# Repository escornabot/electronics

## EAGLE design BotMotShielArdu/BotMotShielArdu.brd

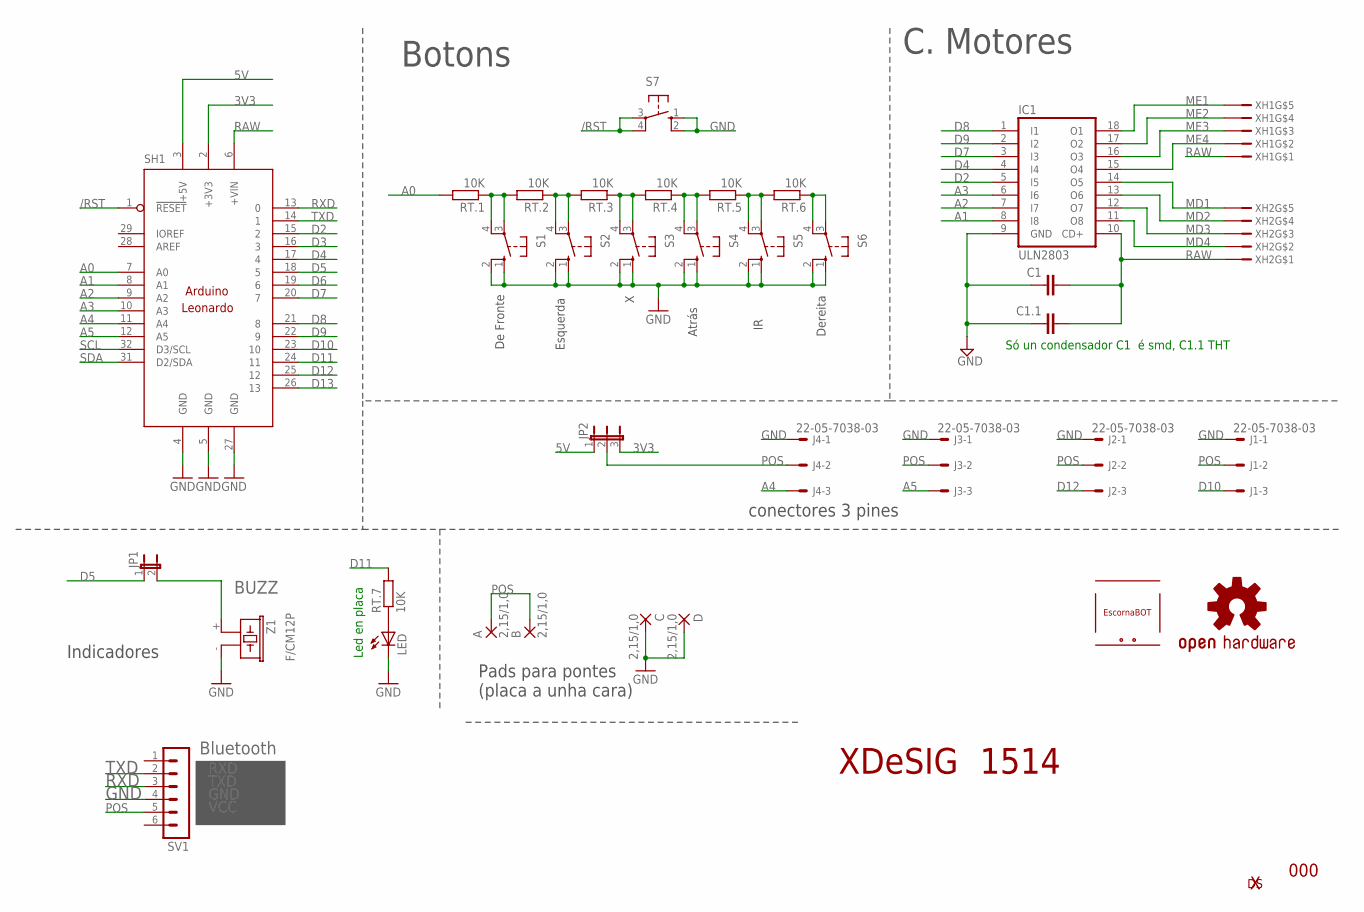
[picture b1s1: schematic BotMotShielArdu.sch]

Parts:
A: 2,15/1,0
B: 2,15/1,0
C: 2,15/1,0
C1: C-EUC1206; C1206
C1.1: C-EU025-024X044; C025-024X044
D: 2,15/1,0
IC1: ULN2803; DIL18
J1, J2, J3, J4: 22-05-7038-03; 7395-03
JP1: JP1E; JP1
JP2: JP2E; JP2
LED: LED5MM
LOGO4: OSHW-LOGOS; OSHW-LOGO-S
RT.1, RT.2, RT.3, RT.4, RT.5, RT.6, RT.7: 10K; 0204/7
S1, S2, S3, S4, S5, S6: B3F-40XX; B3F40XX_NH
S7: 10-XX; B3F-10XX
SH1: ARDUINO_LEONARDO; LEONARDO
SV1: MA06-1
U$1: ESCORNABOT; ESCORNA_PEQUE
U$3: XDESIG1; XDESIG_CU
XH1, XH2: B5B-XH-A
Z1: F/CM12P

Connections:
3V3: JP2.3, SH1.2 (+3V3)
5V: JP2.1, SH1.3 (+5V)
/RST: S7.3, S7.4 (P1), SH1.1 (!RESET)
A0: RT.1.2, SH1.7 (A0)
A1: IC1.8 (I8), SH1.8 (A1)
A2: IC1.7 (I7), SH1.9 (A2)
A3: IC1.6 (I6), SH1.10 (A3)
A4: J4.3, SH1.11 (A4)
A5: J3.3, SH1.12 (A5)
D2: IC1.5 (I5), SH1.15 (2)
D3: SH1.16 (3)
D4: IC1.4 (I4), SH1.17 (4)
D5: JP1.1, SH1.18 (5)
D6: SH1.19 (6)
D7: IC1.3 (I3), SH1.20 (7)
D8: IC1.1 (I1), SH1.21 (8)
D9: IC1.2 (I2), SH1.22 (9)
D10: J1.3, SH1.23 (10)
D11: RT.7.2, SH1.24 (11)
D12: J2.3, SH1.25 (12)
D13: SH1.26 (13)
GND: C.1, C1.1, C1.1.1, D.1, IC1.9 (GND), J1.1, J2.1, J3.1, J4.1, LED.K (C), S1.1 (S), S1.2 (S1), S2.1 (S), S2.2 (S1), S3.1 (S), S3.2 (S1), S4.1 (S), S4.2 (S1), S5.1 (S), S5.2 (S1), S6.1 (S), S6.2 (S1), S7.1 (S), S7.2 (S1), SH1.4 (GND), SH1.5 (GND), SH1.27 (GND), SV1.4, Z1.- (2)
MD1: IC1.14 (O5), XH2.P$5
MD2: IC1.13 (O6), XH2.P$4
MD3: IC1.12 (O7), XH2.P$3
MD4: IC1.11 (O8), XH2.P$2
ME1: IC1.18 (O1), XH1.P$5
ME2: IC1.17 (O2), XH1.P$4
ME3: IC1.16 (O3), XH1.P$3
ME4: IC1.15 (O4), XH1.P$2
unnamed: LED.A, RT.7.1
unnamed: RT.6.1, S6.3, S6.4 (P1)
unnamed: RT.1.1, RT.2.2, S1.3, S1.4 (P1)
unnamed: JP1.2, Z1.+ (1)
unnamed: RT.5.1, RT.6.2, S5.3, S5.4 (P1)
unnamed: RT.4.1, RT.5.2, S4.3, S4.4 (P1)
unnamed: RT.3.1, RT.4.2, S3.3, S3.4 (P1)
unnamed: RT.2.1, RT.3.2, S2.3, S2.4 (P1)
POS: A.1, B.1, J1.2, J2.2, J3.2, J4.2, JP2.2, SV1.5
RAW: C1.2, C1.1.2, IC1.10 (CD+), SH1.6 (+VIN), XH1.P$1, XH2.P$1
RXD: SH1.13 (0), SV1.3
SCL: SH1.32 (D3/SCL)
SDA: SH1.31 (D2/SDA)
TXD: SH1.14 (1), SV1.2

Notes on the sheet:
Só un condensador C1 é smd, C1.1 THT
De Fronte
Esquerda
Dereita
Atrás
Led en placa
BUZZ
Bluetooth
RXD
TXD
GND
VCC
Botons
C. Motores
conectores 3 pines
Indicadores
Pads para pontes (placa a unha cara)
XDeSIG
1514
000

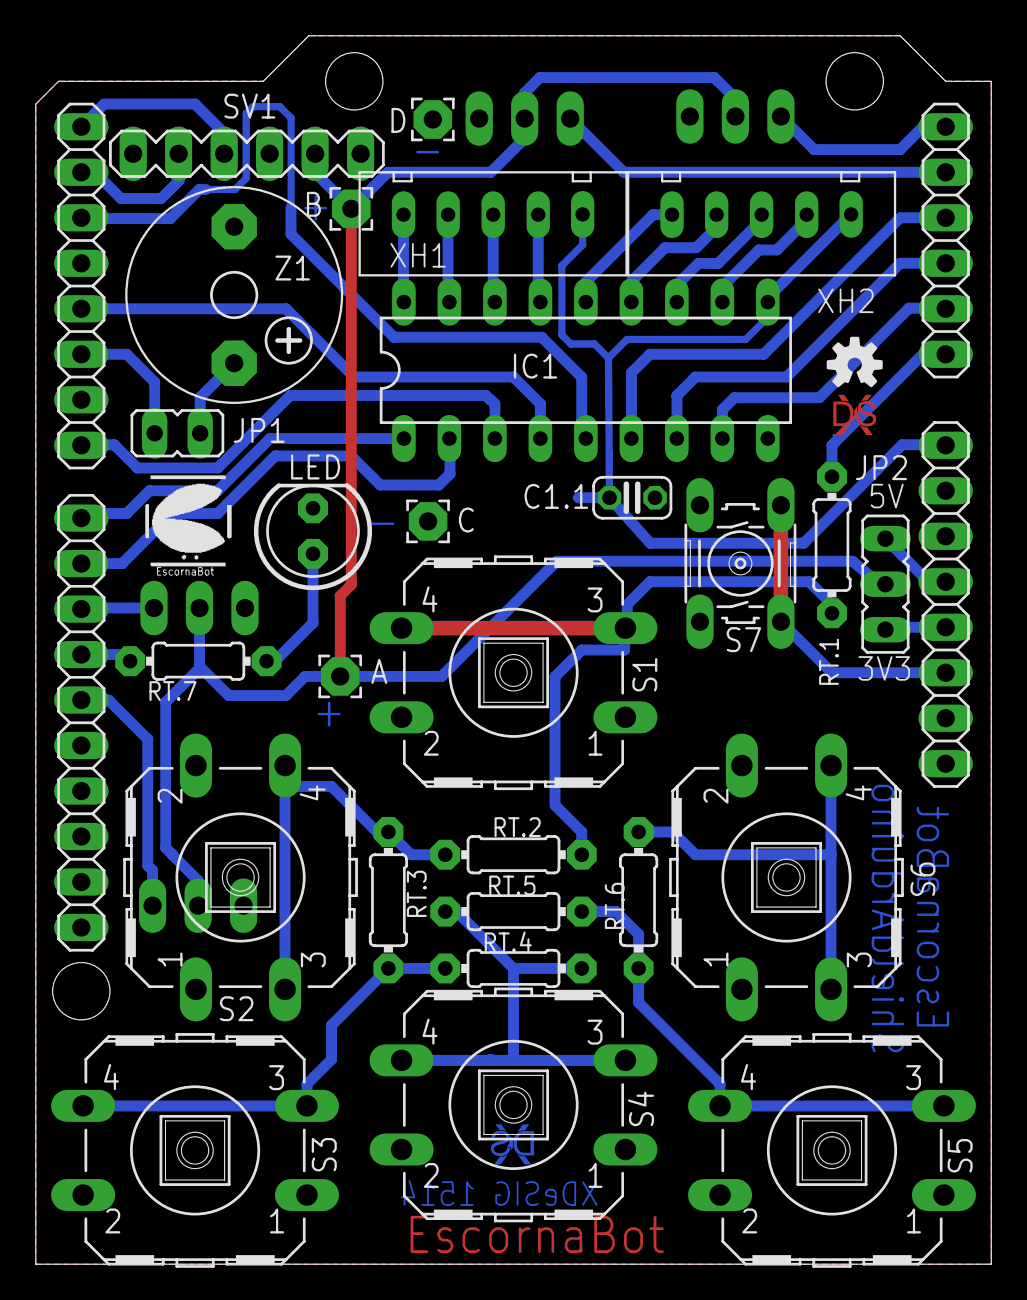
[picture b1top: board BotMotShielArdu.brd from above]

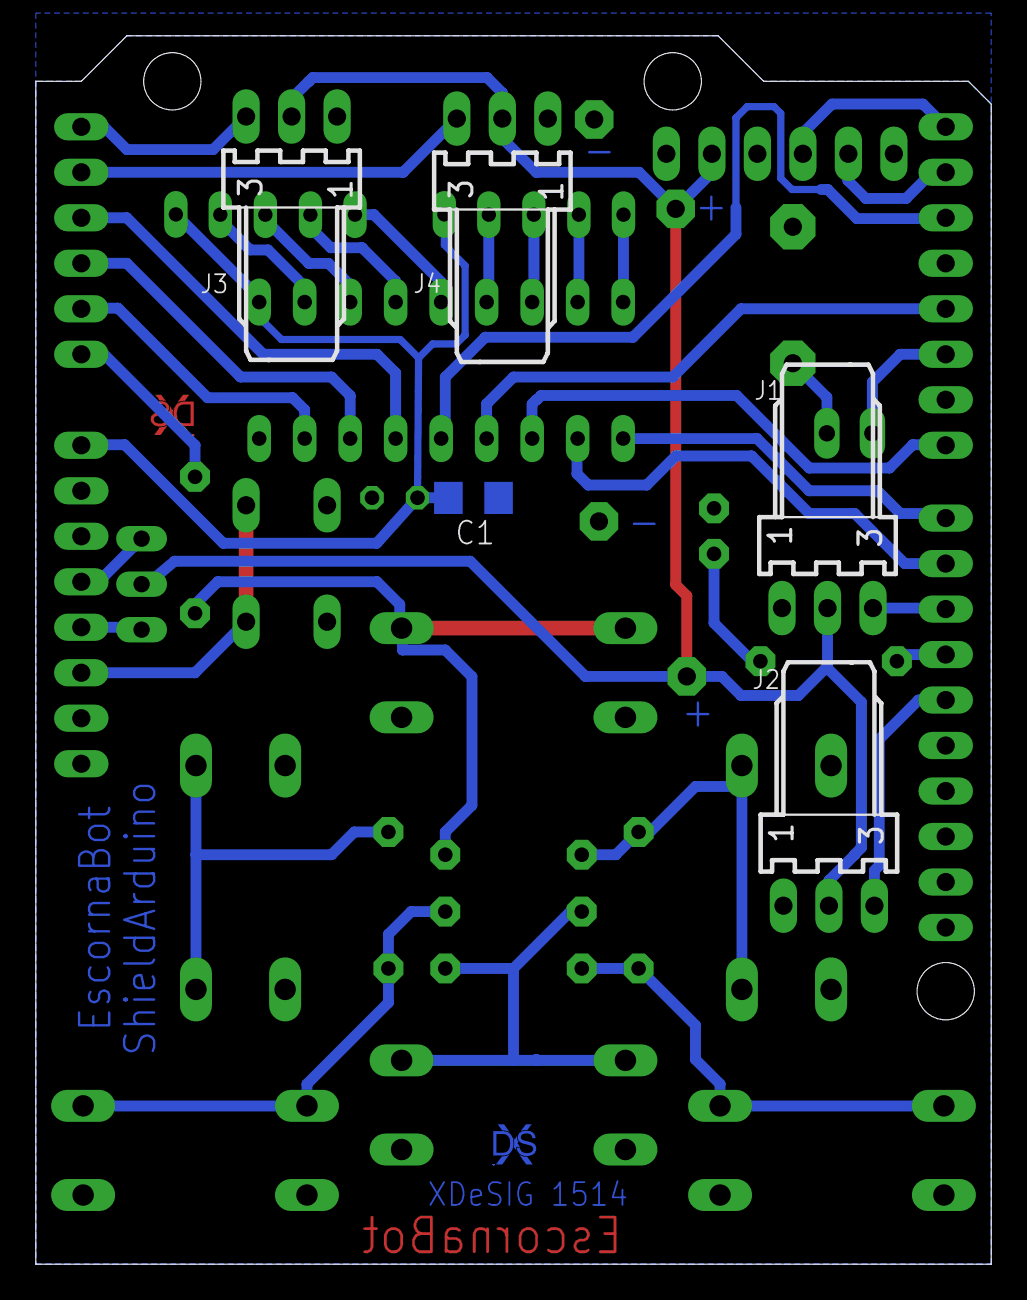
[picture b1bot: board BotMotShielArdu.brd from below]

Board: 2 copper layers, 53.3 x 68.6 mm, 37 parts (6 on the bottom side), 39 nets.

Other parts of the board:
U$2: XDESIG1; XDESIG_CU

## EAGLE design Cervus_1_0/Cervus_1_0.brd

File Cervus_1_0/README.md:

# Cervus version 1.0

* Author: [XDeSIG][SITE]
* License: [Creative Commons BY-SA][CCBYSA]

![Render EscornaShield Keypad][RENDER]

[CCBYSA]: http://creativecommons.org/licenses/by-sa/4.0/
[SITE]: https://sites.google.com/site/xdesig/
[RENDER]: Cervus_1_0.jpg

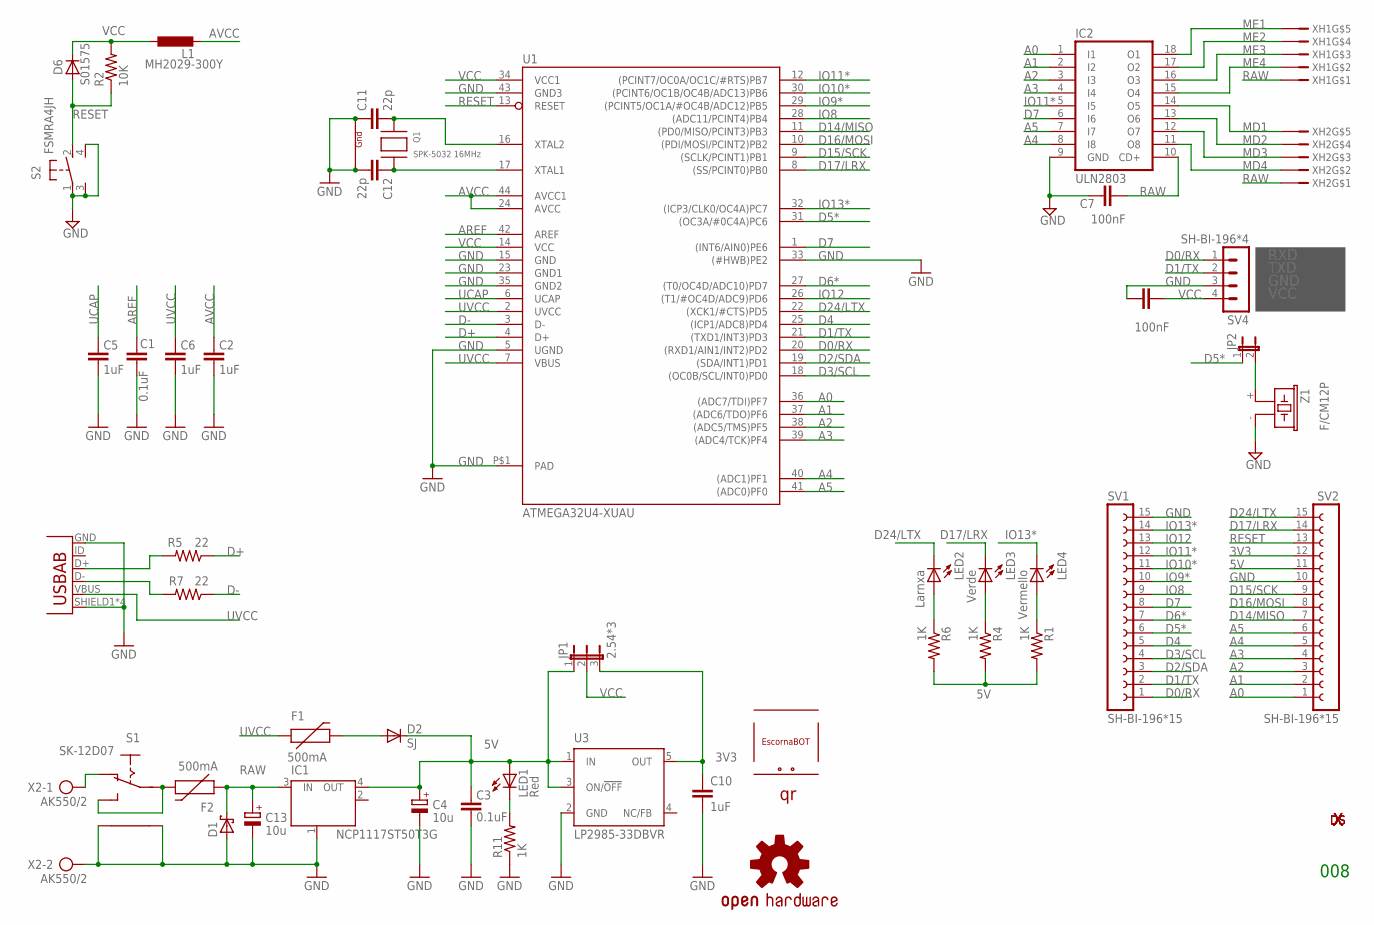
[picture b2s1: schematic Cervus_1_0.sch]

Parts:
C1, C3: 0.1uF; 0603-CAP
C2, C5, C6, C10: 1uF; 0603-CAP
C4, C13: 10u; SMC_B
C7, C8: 100nF; C0603K
C11, C12: 22p; C0603-ROUND
D1: SCHOTTKY-DIODESMA; SMA
D2: SJ; SOD-323
D6: S01575; SOD-323
F1, F2: 500mA; PTC-1206
IC1: NCP1117ST50T3G; SOT223
IC2: ULN2803; DIL18
JP1: 2.54*3; JP2
JP2: JP1E; JP1
L1: MH2029-300Y; L2012C
LED1: Red; LED-0603
LED2: Larnxa; LED-0603
LED3: Verde; LED-0603
LED4: Vermello; LED-0603
LOGO1: OSHW-LOGOS; OSHW-LOGO-S
Q1: SPK-5032 16MHz; NX3225
R1, R4, R6, R11: 1K; 0603-RES
R2: 10K; 0603-RES
R5, R7: 22; 0603-RES
S1: SK-12D07
S2: FSMRA4JH; B3F-31XX
SV1, SV2: SH-BI-196*15; FE15
SV4: SH-BI-196*4; MA04-1
U1: ATMEGA32U4-XUAU; TQFP44-PAD
U2: MICRO USB; USB-AB-MICRO-SMD
U3: LP2985-33DBVR; SOT23-DBV
U$2: XDESIG; XDESIG_CU_2
U$3: ESCORNABOT; ESCORNA_PEQUE
U$5: XDESIG21; XDESIG
U$6: QR25; ESCORNA_QR25
X2: AK550/2
XH1, XH2: XH2.54-5P; B5B-XH-A
Z1: F/CM12P

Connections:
3V3: C10.1, JP1.3, SV2.12, U3.5 (OUT)
5V: C3.2, C4.+, D2.1 (C), IC1.4 (OUT), JP1.1, LED1.A, R1.2, R4.2, R6.2, SV2.11, U3.1 (IN), U3.3 (ON/!OFF)
A0: IC2.1 (I1), SV2.1, U1.36 ((ADC7/TDI)PF7)
A1: IC2.2 (I2), SV2.2, U1.37 ((ADC6/TDO)PF6)
A2: IC2.3 (I3), SV2.3, U1.38 ((ADC5/TMS)PF5)
A3: IC2.4 (I4), SV2.4, U1.39 ((ADC4/TCK)PF4)
A4: IC2.8 (I8), SV2.5, U1.40 ((ADC1)PF1)
A5: IC2.7 (I7), SV2.6, U1.41 ((ADC0)PF0)
AREF: C1.2, U1.42 (AREF)
AVCC: C2.2, L1.2, U1.24 (AVCC), U1.44 (AVCC1)
D0/RX: SV1.1, SV4.1, U1.20 ((RXD1/AIN1/INT2)PD2)
D1/TX: SV1.2, SV4.2, U1.21 ((TXD1/INT3)PD3)
D2/SDA: SV1.3, U1.19 ((SDA/INT1)PD1)
D3/SCL: SV1.4, U1.18 ((OC0B/SCL/INT0)PD0)
D4: SV1.5, U1.25 ((ICP1/ADC8)PD4)
D5*: JP2.1, SV1.6, U1.31 ((OC3A/#0C4A)PC6)
D6*: SV1.7, U1.27 ((T0/OC4D/ADC10)PD7)
D7: IC2.6 (I6), SV1.8, U1.1 ((INT6/AIN0)PE6)
D14/MISO: SV2.7, U1.11 ((PD0/MISO/PCINT3)PB3)
D15/SCK: SV2.9, U1.9 ((SCLK/PCINT1)PB1)
D16/MOSI: SV2.8, U1.10 ((PDI/MOSI/PCINT2)PB2)
D17/LRX: LED3.C, SV2.14, U1.8 ((SS/PCINT0)PB0)
D24/LTX: LED2.C, SV2.15, U1.22 ((XCK1/#CTS)PD5)
D+: R5.1, U1.4 (D+)
D-: R7.1, U1.3 (D-)
GND: C1.1, C2.1, C3.1, C4.-, C5.1, C6.1, C7.1, C8.1, C10.2, C11.1, C12.2, C13.-, D1.A, IC1.1 (GND/ADJ), IC2.9 (GND), Q1.2 (G2), Q1.4 (G1), R11.1, S1.P$4, S1.P$5, S2.1, S2.3 (CH2), S2.4 (CH1), SV1.15, SV2.10, SV4.3, U1.5 (UGND), U1.15 (GND), U1.23 (GND1), U1.33 ((#HWB)PE2), U1.35 (GND2), U1.43 (GND3), U1.P$1 (PAD), U2.GND, U2.SHIELD1 (SHIELD), U2.SHIELD2 (SHIELD), U2.SHIELD3 (SHIELD), U2.SHIELD4 (SHIELD), U3.2 (GND), X2.2, Z1.- (2)
IO8: SV1.9, U1.28 ((ADC11/PCINT4)PB4)
IO9*: SV1.10, U1.29 ((PCINT5/OC1A/#OC4B/ADC12)PB5)
IO10*: SV1.11, U1.30 ((PCINT6/OC1B/OC4B/ADC13)PB6)
IO11*: IC2.5 (I5), SV1.12, U1.12 ((PCINT7/OC0A/OC1C/#RTS)PB7)
IO12: SV1.13, U1.26 ((T1/#OC4D/ADC9)PD6)
IO13*: LED4.C, SV1.14, U1.32 ((ICP3/CLK0/OC4A)PC7)
MD1: IC2.14 (O5), XH2.P$5
MD2: IC2.13 (O6), XH2.P$4
MD3: IC2.12 (O7), XH2.P$3
MD4: IC2.11 (O8), XH2.P$2
ME1: IC2.18 (O1), XH1.P$5
ME2: IC2.17 (O2), XH1.P$4
ME3: IC2.16 (O3), XH1.P$3
ME4: IC2.15 (O4), XH1.P$2
unnamed: F2.2, S1.P$1, S1.P$3 (S)
unnamed: LED2.A, R6.1
unnamed: D2.2 (A), F1.2
unnamed: LED3.A, R4.1
unnamed: LED4.A, R1.1
unnamed: R7.2, U2.D-
unnamed: S1.P$2 (O), X2.1
unnamed: R5.2, U2.D+
unnamed: C12.1, Q1.3 (X2), U1.17 (XTAL1)
unnamed: LED1.C, R11.2
unnamed: JP2.2, Z1.+ (1)
RAW: C7.2, C13.+, D1.C, F2.1, IC1.3 (IN), IC2.10 (CD+), XH1.P$1, XH2.P$1
RESET: D6.2 (A), R2.1, S2.2 (S), SV2.13, U1.13 (RESET)
UCAP: C5.2, U1.6 (UCAP)
UVCC: C6.2, F1.1, U1.2 (UVCC), U1.7 (VBUS), U2.VBUS
VCC: C8.2, D6.1 (C), JP1.2, L1.1, R2.2, SV4.4, U1.14 (VCC), U1.34 (VCC1)
XTAL3: C11.2, Q1.1 (X1), U1.16 (XTAL2)

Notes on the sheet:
RXD
TXD
GND
VCC
008

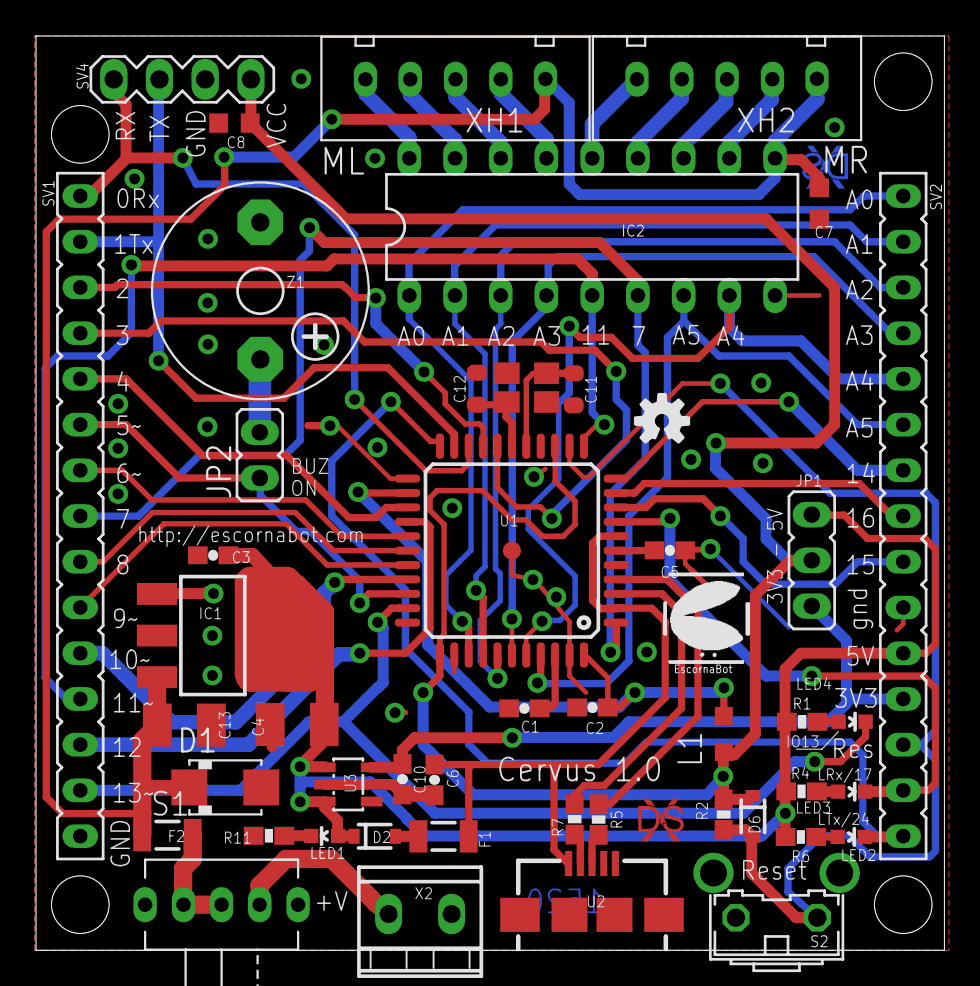
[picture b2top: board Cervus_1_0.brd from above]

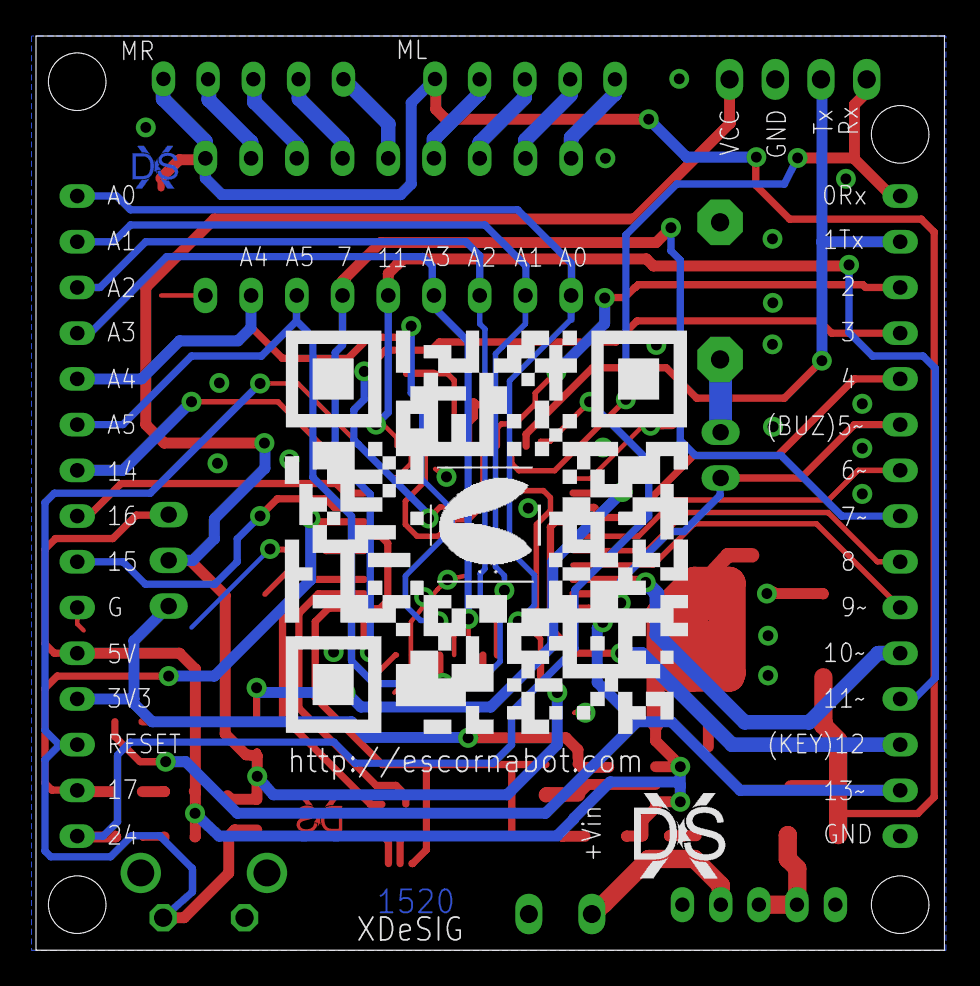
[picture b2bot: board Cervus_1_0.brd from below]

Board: 2 copper layers, 50.5 x 50.8 mm, 52 parts (3 on the bottom side), 57 nets.

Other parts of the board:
U$1: XDESIG; XDESIG_CU_2

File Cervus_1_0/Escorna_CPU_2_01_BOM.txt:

artlist exported from D:/PROXECTOS/Escorna_bot/Escorna_CPU_2.0/Escorna_CPU2_01/Escorna_CPU_2_01.sch at 16/05/2015 20:14:45

Part  Value           Device            Package          Description                                                                                                                                                                                                        MF MPN      OC_FARNELL OC_NEWARK
C1    0.1uF           CAP0603-CAP       0603-CAP         Capacitor
C2    1uF             CAP0603-CAP       0603-CAP         Capacitor
C3    0.1uF           CAP0603-CAP       0603-CAP         Capacitor
C4    10u             CPOL-EUSMCB       SMC_B            POLARIZED CAPACITOR, European symbol
C5    1uF             CAP0603-CAP       0603-CAP         Capacitor
C6    1uF             CAP0603-CAP       0603-CAP         Capacitor
C7    100nF           C-EUC0603K        C0603K           CAPACITOR, European symbol
C8    100nF           C-EUC0603K        C0603K           CAPACITOR, European symbol
C10   1uF             CAP0603-CAP       0603-CAP         Capacitor
C11   22p             C-EUC0603         C0603-ROUND      CAPACITOR, European symbol
C12   22p             C-EUC0603         C0603-ROUND      CAPACITOR, European symbol
C13   10u             CPOL-EUSMCB       SMC_B            POLARIZED CAPACITOR, European symbol
D1                    SCHOTTKY-DIODESMA SMA              Schottky Diode
D2    SJ              DIODESOD          SOD-323          Diode
D6    S01575          DIODESOD          SOD-323          Diode
F1    500mA           PTCSMD            PTC-1206         Resettable Fuse PTC
F2    500mA           PTCSMD            PTC-1206         Resettable Fuse PTC
IC1   NCP1117ST50T3G  MC33269ST-3.3T3   SOT223           Adjustable Output Low Dropout Voltage Regulator 800 mA
IC2   ULN2803         ULN2803A"         DIL18            DRIVER ARRAY
JP1   2.54*3          JP2E              JP2              JUMPER
JP2                   JP1E              JP1              JUMPER
L1    MH2029-300Y     L-EUL2012C        L2012C           INDUCTOR, European symbol
LED1  Red             LED0603           LED-0603         LEDs
LED2  Larnxa          LED0603           LED-0603         LEDs
LED3  Verde           LED0603           LED-0603         LEDs
LED4  Vermello        LED0603           LED-0603         LEDs
Q1    SPK-5032 16MHz  XTAL-4-3225       NX3225           Classic 4-pin 3.2 x 2.5mm crystal
R1    1K              RESISTOR0603-RES  0603-RES         Resistor
R2    10K             RESISTOR0603-RES  0603-RES         Resistor
R4    1K              RESISTOR0603-RES  0603-RES         Resistor
R5    22              RESISTOR0603-RES  0603-RES         Resistor
R6    1K              RESISTOR0603-RES  0603-RES         Resistor
R7    22              RESISTOR0603-RES  0603-RES         Resistor
R11   1K              RESISTOR0603-RES  0603-RES         Resistor
S1    SK-12D07        SK12F14D          SK-12D07
S2    FSMRA4JH        31-XX             B3F-31XX
SV1   SH-BI-196*15    FE15-1            FE15             FEMALE HEADER                                                                                                                                                                                                                  unknown    unknown
SV2   SH-BI-196*15    FE15-1            FE15             FEMALE HEADER                                                                                                                                                                                                                  unknown    unknown
SV4   SH-BI-196*4     MA04-1            MA04-1           PIN HEADER                                                                                                                                                                                                                     unknown    unknown

U1    ATMEGA32U4-XUAU ATMEGA32U4-XUAU   TQFP44-PAD
U2    MICRO USB       USB-AB            USB-AB-MICRO-SMD This is a USB AB connector that is compatible with USB OTG. i.e. this connector can serve as a host or device
U3    LP2985-33DBVR   LP2985-XXDBVR33   SOT23-DBV        ULTRALOW-POWER 50-mA LOW-DROPOUT LINEAR REGULATORS
X2    AK550/2         AK550/2           AK550/2          CONNECTOR                                                                                                                                                                                                                      unknown    unknown
XH1   XH2.54-5P       B5B-XH-A          B5B-XH-A
XH2   XH2.54-5P       B5B-XH-A          B5B-XH-A
Z1    F/CM12P         F/CM12P           F/CM12P          BUZZER 12mm Source: Buerklin                                                                                                                                                                                                        unknown    unknown

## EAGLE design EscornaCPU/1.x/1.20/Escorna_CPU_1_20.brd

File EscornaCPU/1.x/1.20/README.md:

## Escorna CPU 1.20

It allows to include an Arduino Uno for the control of the robot, an ESP-01 or Bluetooth (for communications).
You can connect them to different keypads to manage the robot, I recommend the [E_KEYPAD_2.20]

## License

Every content in this repo, otherwise specified under subdirectories, is
licensed under [CERN Open Hardware Licence -W- V2][OHL-W-V2].
(by [XDeSIG][XDE01])

## To buy boards

Developer doesn't produce boards to get money. [provider]

Are you a board provider? Please, send us your buyer's guide! xdesig@gmail.com

[XDE01]: https://twitter.com/xdesig
[provider]: https://www.pcbway.com/project/shareproject/W50475ASN23_Escorna_CPU_1_20.html
[LICENSEcc]: https://creativecommons.org/licenses/by-sa/3.0/es
[OHL-W-V2]: https://ohwr.org/project/cernohl/wikis/Documents/CERN-OHL-version-2
[E_KEYPAD_2.20]: https://github.com/xdesig/escornabot-electronics/tree/master/Electronics/E_KEYPAD/E_KEYPAD_2.20

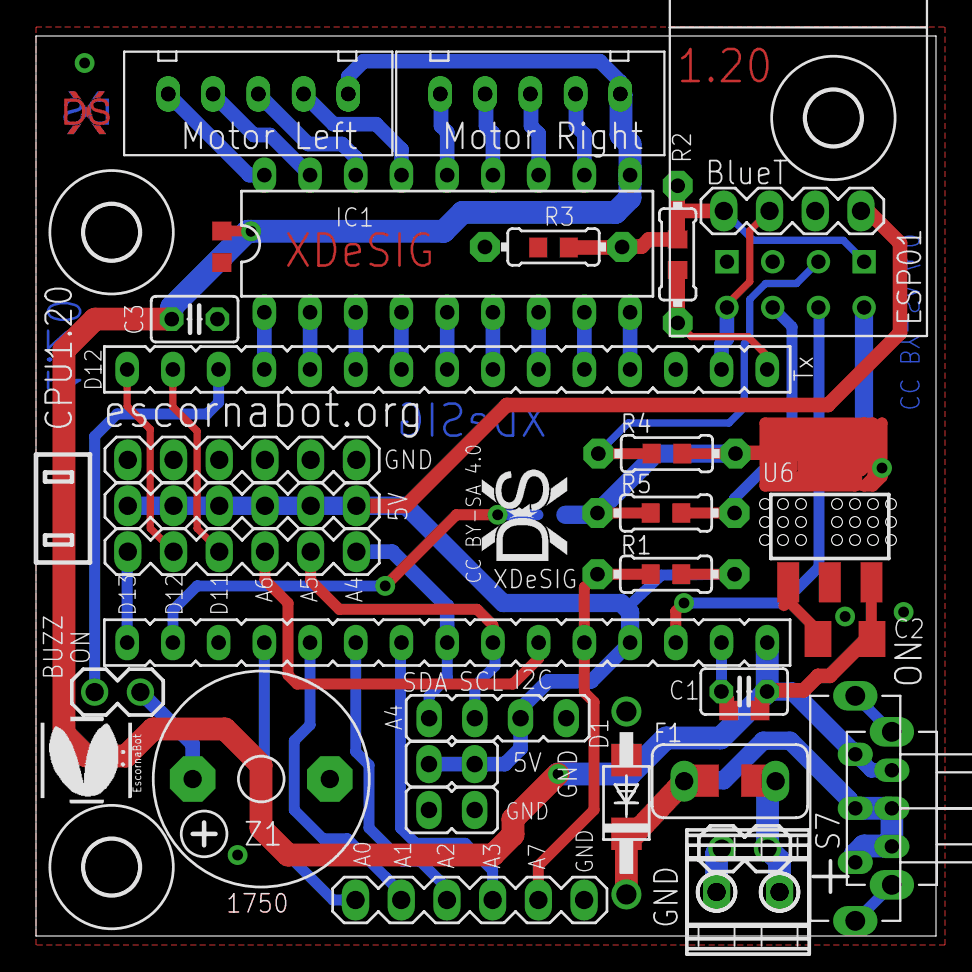
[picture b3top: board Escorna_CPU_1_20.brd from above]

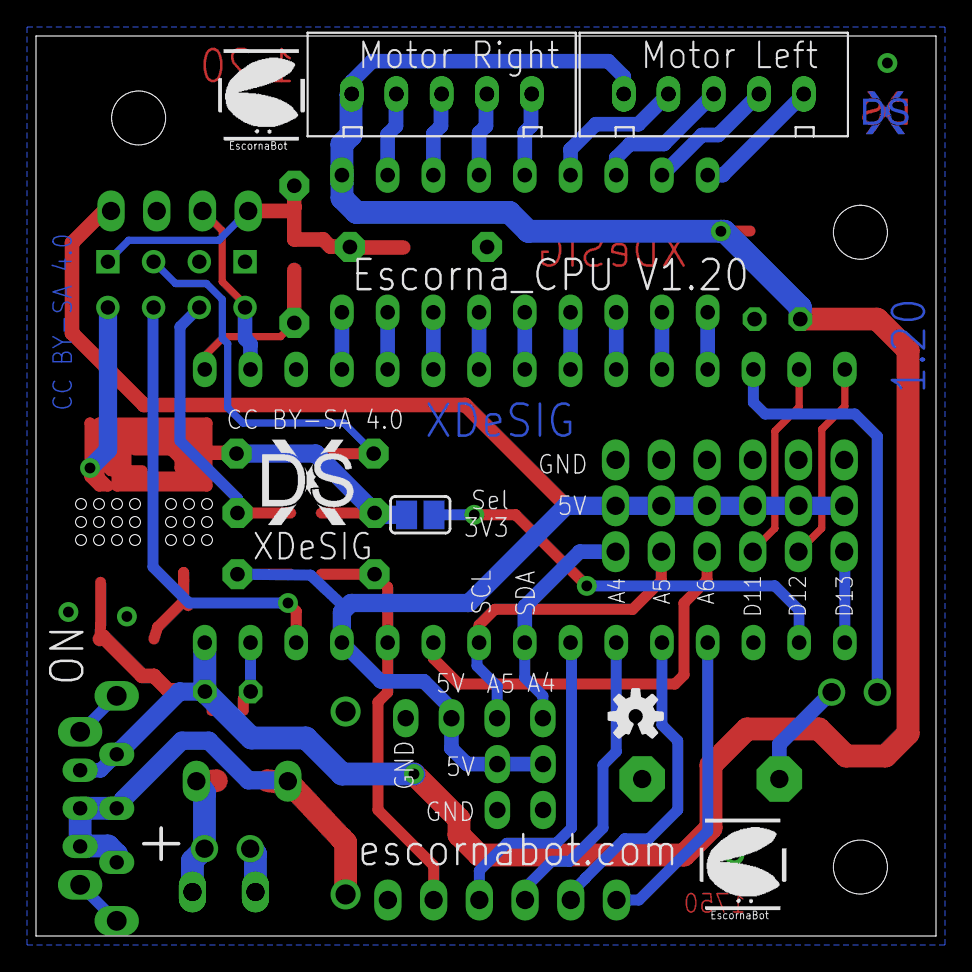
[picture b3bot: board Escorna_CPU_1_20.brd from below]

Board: 2 copper layers, 50.0 x 50.0 mm, 55 parts (8 on the bottom side), 44 nets.

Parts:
C1, C3: 100nF; C025-025X050
C1.1, C3.1: 100nF; C0603K
C2: 1uF; C1206K
D1: 1N5817; DO41-10
D1.1: M7; SMA-DO214AC
ESC, ESC1, ESC2: ESCORNABOT; ESCORNA_PEQUE
F1: PFRA.050; TE5
F1.1: PolySwitch; R1206
H3, H4: H3.0; 3,0
H7: MOUNT-HOLE3.0; 3,0
IC1: ULN2803; DIL18
JP1, JP2: 1X02
JP3, JP4: JP1
JP5: JP4
LOGO2: OSHW-LOGOS; OSHW-LOGO-S
R1, R2, R4, R5: 10K; 0204/7
R1.1, R2.1, R4.1, R5.1: 10K; R0603
R3: 18K; 0204/7
R3.1: 18K; R0603
S7: SK12F14; ESCORNA_SK-12F14-G
S7.1: SK12D07; ESCORNA_SK-12D07
SJ1: SJ
SV1, SV2: 1x15 SOCKET STRIP; CON-LSTA_FE15
SV3, SV4, SV5, SV6: MA06-1
U2: ESP01
U3: MA04-1
U6: 1117-3.3; SOT223
U$1, U$13: XDESIG_XDESIG21; XDESIG_XDESIG
X1, X1.1: AK550/2
XDS, XDS1: XDESIG; XDESIG_CU_2
XH1, XH2, XH3, XH4: B5B-XH-A
Z1: CFG12; F/CM12P

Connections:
3.3V: SJ1.2, SV2.14
3V3: R4.1, R4.1.1, R5.1, R5.1.1, SJ1.1, U2.VCC, U6.4
5V: JP3.1, JP3.2, JP5.3, R1.1, R1.1.1, SV2.4, SV4.1, SV4.2, SV4.3, SV4.4, SV4.5, SV4.6, U3.4
A0: SV2.12, SV6.1
A1: SV2.11, SV6.2
A2: SV2.10, SV6.3
A3: SV2.9, SV6.4
A4: JP5.1, SV2.8, SV3.1
A5: JP5.2, SV2.7, SV3.2
A6: SV2.6, SV3.3
A7: R1.2, R1.1.2, SV2.5, SV6.5
CH: R4.2, R4.1.2, U2.GPIO0
D2: IC1.8, SV1.5
D3: IC1.7, SV1.6
D4: IC1.6, SV1.7
D5: IC1.5, SV1.8
D6: IC1.4, SV1.9
D7: IC1.3, SV1.10
D8: IC1.2, SV1.11
D9: IC1.1, SV1.12
D10: JP1.2, SV1.13
D11: SV1.14, SV3.4
D12: SV1.15, SV3.5
D13: SV2.15, SV3.6
GND: C1.2, C1.1.1, C2.1, C3.1, C3.1.1, D1.A, D1.1.A, IC1.9, JP2.1, JP4.1, JP4.2, JP5.4, R3.2, R3.1.1, SV1.4, SV2.2, SV5.1, SV5.2, SV5.3, SV5.4, SV5.5, SV5.6, SV6.6, U2.GND, U3.3, U6.1, X1.1, X1.1.2, Z1.-
ML1: IC1.18, XH1.P$5, XH3.P$5
ML2: IC1.17, XH1.P$4, XH3.P$4
ML3: IC1.16, XH1.P$3, XH3.P$3
ML4: IC1.15, XH1.P$2, XH3.P$2
MR1: IC1.14, XH2.P$5, XH4.P$5
MR2: IC1.13, XH2.P$4, XH4.P$4
MR3: IC1.12, XH2.P$3, XH4.P$3
MR4: IC1.11, XH2.P$2, XH4.P$2
unnamed: R5.2, R5.1.2, U2.CH_PD
unnamed: JP1.1, Z1.+
unnamed: F1.1, F1.1.1, JP2.2, X1.2, X1.1.1
unnamed: S7.P$4, S7.1.P$4
unnamed: S7.P$5, S7.1.P$5
RAW: C1.1, C1.1.2, C2.2, C3.2, C3.1.2, IC1.10, S7.P$2, S7.1.P$2, SV2.1, U6.3, XH1.P$1, XH2.P$1, XH3.P$1, XH4.P$1
RST: SV2.3, U2.RST
RX: SV1.2, U2.TX, U3.2
TX: R2.1, R2.1.1, SV1.1
TX3V3: R2.2, R2.1.2, R3.1, R3.1.2, U2.RX, U3.1
VIN: D1.C, D1.1.K, F1.2, F1.1.2, S7.P$1, S7.P$3, S7.1.P$1, S7.1.P$3

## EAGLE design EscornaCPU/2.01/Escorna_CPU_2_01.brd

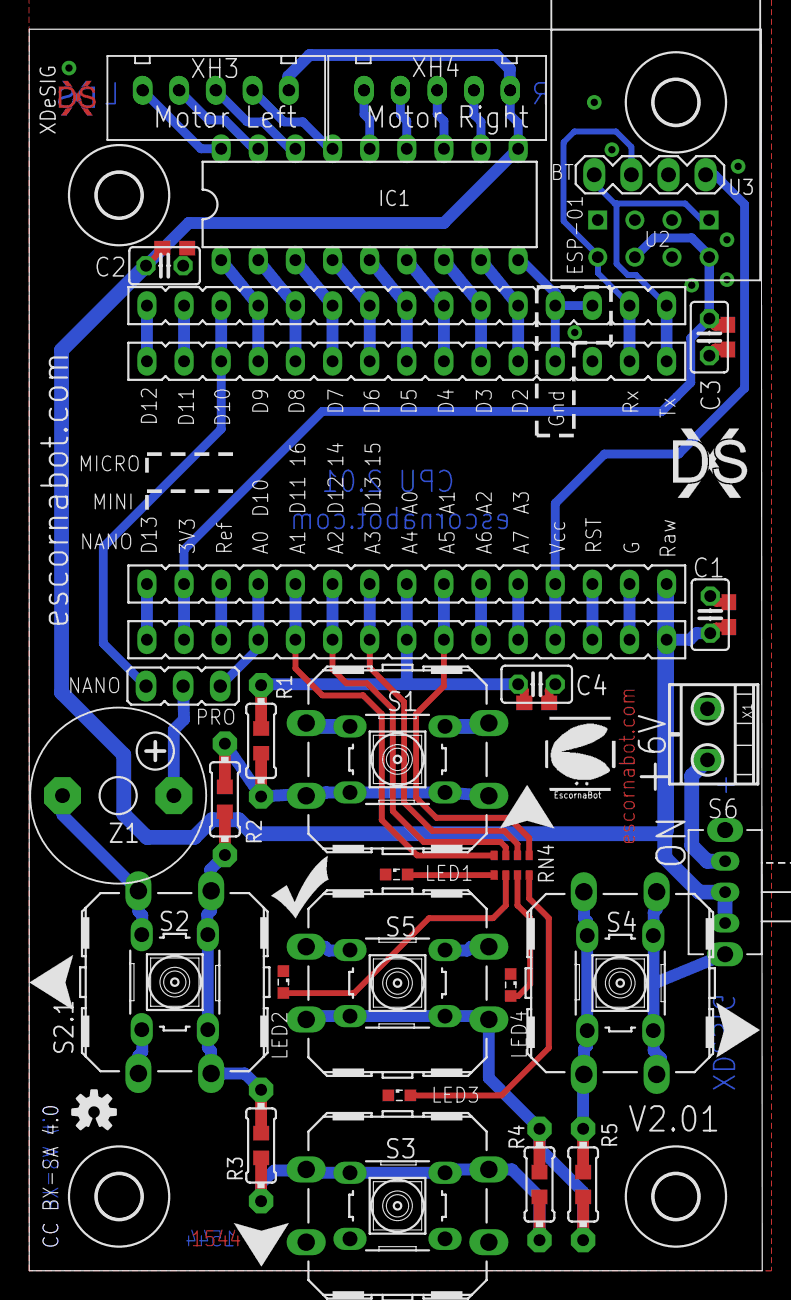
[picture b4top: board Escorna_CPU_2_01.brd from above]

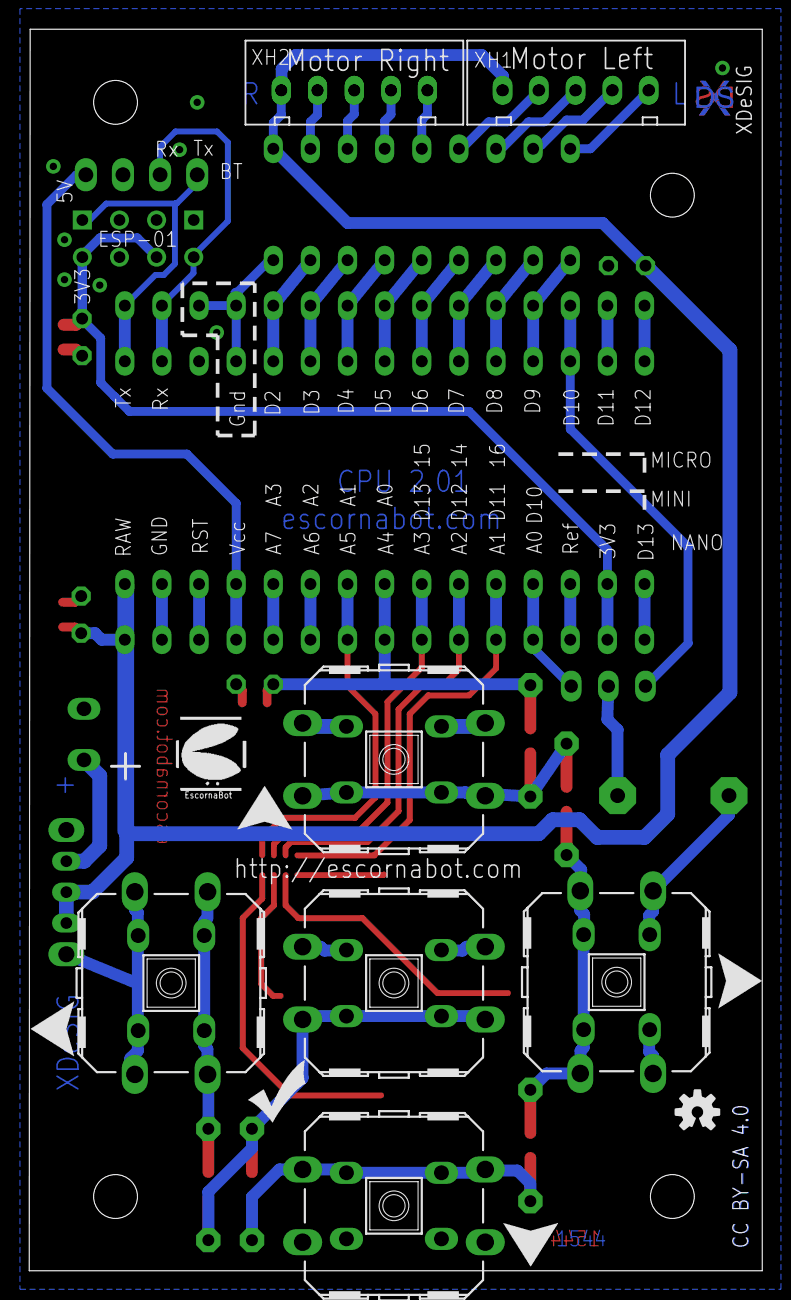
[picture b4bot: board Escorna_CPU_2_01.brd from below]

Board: 2 copper layers, 50.2 x 85.0 mm, 69 parts (10 on the bottom side), 47 nets.

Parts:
C1, C2, C3: 100nF; C025-025X050
C1.1, C2.1, C3.1: 100nF; C0603
C4: 10nF; C025-025X050
C4.1: 10nF; C0603
ESC: ESCORNABOT; ESCORNA_PEQUE
H1, H2, H3, H4: MOUNT-HOLE3.0; 3,0
IC1: ULN2803; DIL18
JP2: JP2
LED1, LED2, LED3, LED4: LED_SML0603
LOGO1, LOGO2: OSHW-LOGOS; OSHW-LOGO-S
PH1, PH2, PH3, PH4: FE15
R1, R2, R3, R4, R5: 10K; 0204/7
R1.1, R2.1, R3.1, R4.1, R5.1: 10K; R0603
RN4: 1K; CAY16
S1, S2, S3, S4, S5: B3F-10XX
S1.1, S2.1, S3.1, S4.1, S5.1: SWITCH-OMRON_B3F40XX_NH
S6: SK-12D07
U2: ESP01
U3: MA04-1
U$1, U$3, U$4, U$6, U$7, U$8, U$9, U$11: FRECHA
U$2, U$10: GO; VALE
U$5: ESCORNABOT; ESCORNA_PEQUE
U$12: XDESIG_XDESIG21; XDESIG_XDESIG
X1: AK550/2
XDS, XDS1: XDESIG; XDESIG_CU_2
XH1, XH2, XH3, XH4: B5B-XH-A
Z1: CFG12; F/CM12P

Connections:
3V3: C3.1, C3.1.1, PH2.14, PH4.14, U2.CH_PD, U2.VCC
5V: PH2.4, PH4.4, U3.4
A0: JP2.1, PH2.12, PH4.12
A1: PH2.11, PH4.11, RN4.4
A2: PH2.10, PH4.10, RN4.3
A3: PH2.9, PH4.9, RN4.2
A4: C4.2, C4.1.2, PH2.8, PH4.8, R1.2, R1.1.2
A5: PH2.7, PH4.7, RN4.1
A6: PH2.6, PH4.6
A7: PH2.5, PH4.5
AREF: PH2.13, PH4.13
D2: IC1.8, PH1.5, PH3.5
D3: IC1.7, PH1.6, PH3.6
D4: IC1.6, PH1.7, PH3.7
D5: IC1.5, PH1.8, PH3.8
D6: IC1.4, PH1.9, PH3.9
D7: IC1.3, PH1.10, PH3.10
D8: IC1.2, PH1.11, PH3.11
D9: IC1.1, PH1.12, PH3.12
D10: JP2.3, PH1.13, PH3.13
D11: PH1.14, PH3.14
D12: PH1.15, PH3.15
D13: PH2.15, PH4.15
GND: C1.2, C1.1.1, C2.1, C2.1.1, C3.2, C3.1.2, C4.1, C4.1.1, IC1.9, LED1.C, LED2.C, LED3.C, LED4.C, PH1.4, PH2.2, PH3.3, PH3.4, PH4.2, S1.1, S1.2, S1.1.1, S1.1.2, S2.1, S2.2, S2.1.1, S2.1.2, S3.1, S3.2, S3.1.1, S3.1.2, S4.1, S4.2, S4.1.1, S4.1.2, S5.1, S5.2, S5.1.1, S5.1.2, S6.P$4, S6.P$5, U2.GND, U3.3, X1.2, Z1.-
ML1: IC1.18, XH1.P$5, XH3.P$5
ML2: IC1.17, XH1.P$4, XH3.P$4
ML3: IC1.16, XH1.P$3, XH3.P$3
ML4: IC1.15, XH1.P$2, XH3.P$2
MR1: IC1.14, XH2.P$5, XH4.P$5
MR2: IC1.13, XH2.P$4, XH4.P$4
MR3: IC1.12, XH2.P$3, XH4.P$3
MR4: IC1.11, XH2.P$2, XH4.P$2
unnamed: JP2.2, Z1.+
unnamed: S6.P$2, X1.1
unnamed: LED1.A, RN4.5
unnamed: LED2.A, RN4.6
unnamed: LED4.A, RN4.7
unnamed: LED3.A, RN4.8
RAW: C1.1, C1.1.2, C2.2, C2.1.2, IC1.10, PH2.1, PH4.1, S6.P$1, S6.P$3, XH1.P$1, XH2.P$1, XH3.P$1, XH4.P$1
RST: PH2.3, PH4.3
RX: PH1.2, PH3.2, U2.TX, U3.2
S1: R1.1, R1.1.1, R2.2, R2.1.2, S1.3, S1.4, S1.1.3, S1.1.4
S2: R2.1, R2.1.1, R3.2, R3.1.2, S2.3, S2.4, S2.1.3, S2.1.4
S3: R3.1, R3.1.1, R4.2, R4.1.2, S3.3, S3.4, S3.1.3, S3.1.4
S4: R4.1, R4.1.1, R5.2, R5.1.2, S5.3, S5.4, S5.1.3, S5.1.4
S5: R5.1, R5.1.1, S4.3, S4.4, S4.1.3, S4.1.4
TX: PH1.1, PH3.1, U2.RX, U3.1

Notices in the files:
EscornaCPU/1.x/1.20/Escorna_CPU_1_20.brd:
Attribution-ShareAlike 4.0 International (CC BY-SA 4.0)
CC BY-SA 4.0
parts and their libraries:
SparkFun-Aesthetics: Licensing: CC v3.0 Share-Alike You are welcome to use this library for commercial purposes.
SparkFun-Connectors: Licensing: Creative Commons ShareAlike 4.0 International - https://creativecommons.org/licenses/by-sa/4.0
